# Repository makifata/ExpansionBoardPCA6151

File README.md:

# ExpansionBoardPCA6151
PCA-6151 does work with 5V / 12V supply with four pin connector. However, 
Peripheral board on ISA bus will need negative voltage such as -12 or -5V. 
This Repo is the custom ISA expansion board which distribute -12V and -5V from ATX power.

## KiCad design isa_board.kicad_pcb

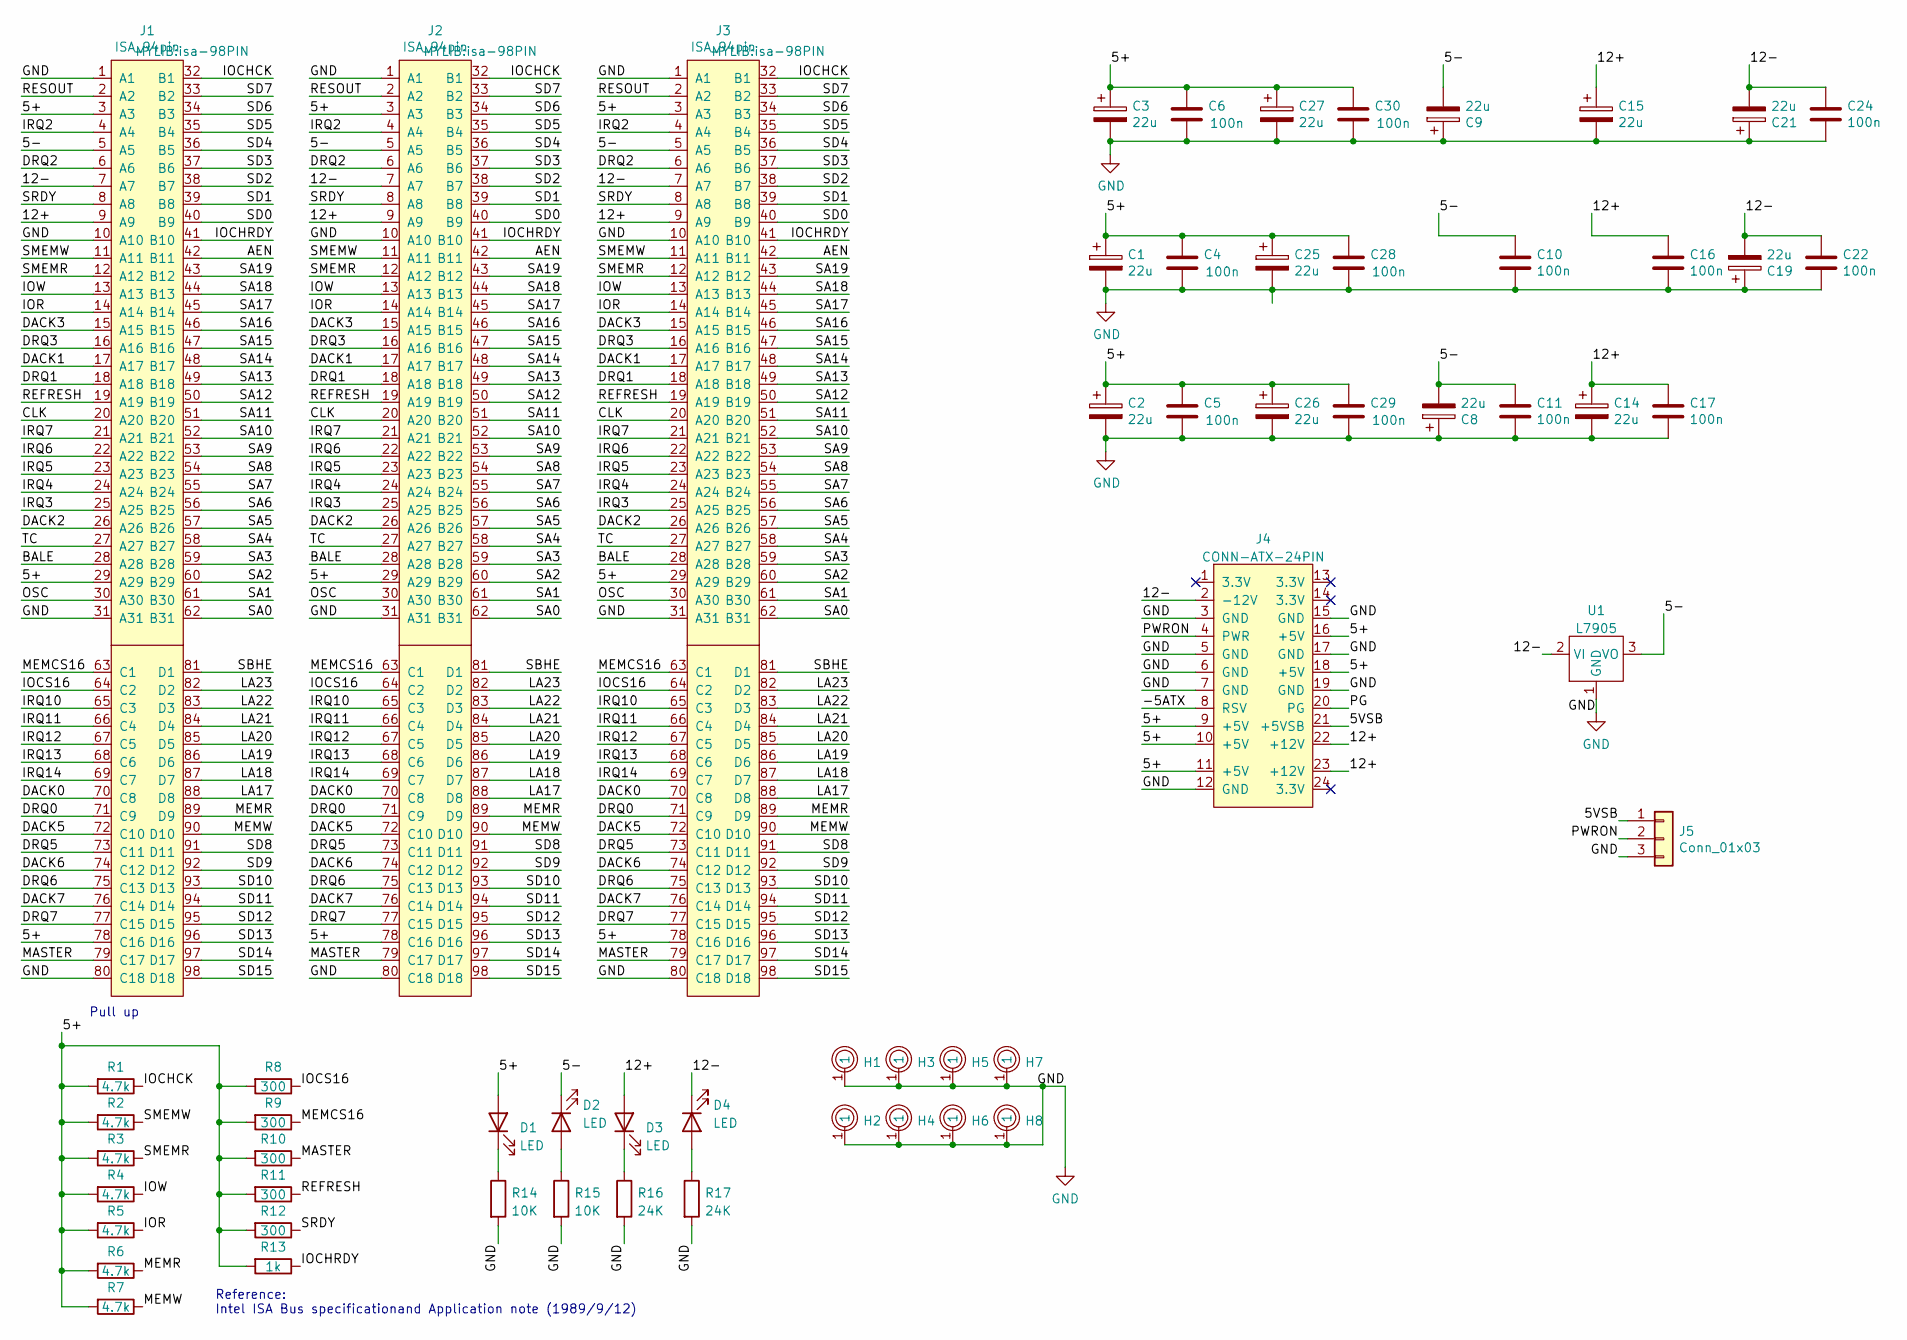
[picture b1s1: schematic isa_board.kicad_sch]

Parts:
C1, C2, C3, C8, C9, C14, C15, C19, C21, C25, C26, C27: 22u; CP_Radial_D5.0mm_P2.00mm
C4, C5, C6, C10, C11, C16, C17, C22, C24, C28, C29, C30: 100n; C_Disc_D4.7mm_W2.5mm_P5.00mm
D1, D2, D3, D4: LED; D_0805_2012Metric_Pad1.15x1.40mm_HandSolder
H1, H2, H3, H4, H5, H6, H7, H8: MountHole; RightAngle
J1, J2, J3: ISA_94pin; isa-98PIN
J4: CONN-ATX-24PIN; atx-24PIN
J5: Conn_01x03; PinHeader_1x03_P2.54mm_Vertical
R1, R2, R3, R4, R5, R6, R7: 4.7k; R_Axial_DIN0309_L9.0mm_D3.2mm_P12.70mm_Horizontal
R8, R9, R10, R11, R12: 300; R_Axial_DIN0309_L9.0mm_D3.2mm_P12.70mm_Horizontal
R13: 1k; R_Axial_DIN0309_L9.0mm_D3.2mm_P12.70mm_Horizontal
R14, R15: 10K; R_0603_1608Metric_Pad0.98x0.95mm_HandSolder
R16, R17: 24K; R_0603_1608Metric_Pad0.98x0.95mm_HandSolder
U1: L7905; L7905ACD2T-TR

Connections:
/5+: C1.1, C2.1, C3.1, C4.1, C5.1, C6.1, C25.1, C26.1, C27.1, C28.1, C29.1, C30.1, D1.2 (A), J1.3 (A3), J1.29 (A29), J1.78 (C16), J2.3 (A3), J2.29 (A29), J2.78 (C16), J3.3 (A3), J3.29 (A29), J3.78 (C16), J4.9 (+5V), J4.10 (+5V), J4.11 (+5V), J4.16 (+5V), J4.18 (+5V), R1.2, R2.2, R3.2, R4.2, R5.2, R6.2, R7.2, R8.2, R9.2, R10.2, R11.2, R12.2, R13.2
/5VSB: J4.21 (+5VSB), J5.1
/12+: C14.1, C15.1, C16.1, C17.1, D3.2 (A), J1.9 (A9), J2.9 (A9), J3.9 (A9), J4.22 (+12V), J4.23 (+12V)
/-5ATX: J4.8 (RSV)
/AEN: J1.42 (B11), J2.42 (B11), J3.42 (B11)
/BALE: J1.28 (A28), J2.28 (A28), J3.28 (A28)
/CLK: J1.20 (A20), J2.20 (A20), J3.20 (A20)
/DACK0: J1.70 (C8), J2.70 (C8), J3.70 (C8)
/DACK1: J1.17 (A17), J2.17 (A17), J3.17 (A17)
/DACK2: J1.26 (A26), J2.26 (A26), J3.26 (A26)
/DACK3: J1.15 (A15), J2.15 (A15), J3.15 (A15)
/DACK5: J1.72 (C10), J2.72 (C10), J3.72 (C10)
/DACK6: J1.74 (C12), J2.74 (C12), J3.74 (C12)
/DACK7: J1.76 (C14), J2.76 (C14), J3.76 (C14)
/DRQ0: J1.71 (C9), J2.71 (C9), J3.71 (C9)
/DRQ1: J1.18 (A18), J2.18 (A18), J3.18 (A18)
/DRQ2: J1.6 (A6), J2.6 (A6), J3.6 (A6)
/DRQ3: J1.16 (A16), J2.16 (A16), J3.16 (A16)
/DRQ5: J1.73 (C11), J2.73 (C11), J3.73 (C11)
/DRQ6: J1.75 (C13), J2.75 (C13), J3.75 (C13)
/DRQ7: J1.77 (C15), J2.77 (C15), J3.77 (C15)
/IOCHCK: J1.32 (B1), J2.32 (B1), J3.32 (B1), R1.1
/IOCHRDY: J1.41 (B10), J2.41 (B10), J3.41 (B10), R13.1
/IOCS16: J1.64 (C2), J2.64 (C2), J3.64 (C2), R8.1
/IOR: J1.14 (A14), J2.14 (A14), J3.14 (A14), R5.1
/IOW: J1.13 (A13), J2.13 (A13), J3.13 (A13), R4.1
/IRQ2: J1.4 (A4), J2.4 (A4), J3.4 (A4)
/IRQ3: J1.25 (A25), J2.25 (A25), J3.25 (A25)
/IRQ4: J1.24 (A24), J2.24 (A24), J3.24 (A24)
/IRQ5: J1.23 (A23), J2.23 (A23), J3.23 (A23)
/IRQ6: J1.22 (A22), J2.22 (A22), J3.22 (A22)
/IRQ7: J1.21 (A21), J2.21 (A21), J3.21 (A21)
/IRQ10: J1.65 (C3), J2.65 (C3), J3.65 (C3)
/IRQ11: J1.66 (C4), J2.66 (C4), J3.66 (C4)
/IRQ12: J1.67 (C5), J2.67 (C5), J3.67 (C5)
/IRQ13: J1.68 (C6), J2.68 (C6), J3.68 (C6)
/IRQ14: J1.69 (C7), J2.69 (C7), J3.69 (C7)
/LA17: J1.88 (D8), J2.88 (D8), J3.88 (D8)
/LA18: J1.87 (D7), J2.87 (D7), J3.87 (D7)
/LA19: J1.86 (D6), J2.86 (D6), J3.86 (D6)
/LA20: J1.85 (D5), J2.85 (D5), J3.85 (D5)
/LA21: J1.84 (D4), J2.84 (D4), J3.84 (D4)
/LA22: J1.83 (D3), J2.83 (D3), J3.83 (D3)
/LA23: J1.82 (D2), J2.82 (D2), J3.82 (D2)
/MASTER: J1.79 (C17), J2.79 (C17), J3.79 (C17), R10.1
/MEMCS16: J1.63 (C1), J2.63 (C1), J3.63 (C1), R9.1
/MEMR: J1.89 (D9), J2.89 (D9), J3.89 (D9), R6.1
/MEMW: J1.90 (D10), J2.90 (D10), J3.90 (D10), R7.1
/OSC: J1.30 (A30), J2.30 (A30), J3.30 (A30)
/PG: J4.20 (PG)
/PWRON: J4.4 (PWR), J5.2
/REFRESH: J1.19 (A19), J2.19 (A19), J3.19 (A19), R11.1
/RESOUT: J1.2 (A2), J2.2 (A2), J3.2 (A2)
/SA0: J1.62 (B31), J2.62 (B31), J3.62 (B31)
/SA1: J1.61 (B30), J2.61 (B30), J3.61 (B30)
/SA2: J1.60 (B29), J2.60 (B29), J3.60 (B29)
/SA3: J1.59 (B28), J2.59 (B28), J3.59 (B28)
/SA4: J1.58 (B27), J2.58 (B27), J3.58 (B27)
/SA5: J1.57 (B26), J2.57 (B26), J3.57 (B26)
/SA6: J1.56 (B25), J2.56 (B25), J3.56 (B25)
/SA7: J1.55 (B24), J2.55 (B24), J3.55 (B24)
/SA8: J1.54 (B23), J2.54 (B23), J3.54 (B23)
/SA9: J1.53 (B22), J2.53 (B22), J3.53 (B22)
/SA10: J1.52 (B21), J2.52 (B21), J3.52 (B21)
/SA11: J1.51 (B20), J2.51 (B20), J3.51 (B20)
/SA12: J1.50 (B19), J2.50 (B19), J3.50 (B19)
/SA13: J1.49 (B18), J2.49 (B18), J3.49 (B18)
/SA14: J1.48 (B17), J2.48 (B17), J3.48 (B17)
/SA15: J1.47 (B16), J2.47 (B16), J3.47 (B16)
/SA16: J1.46 (B15), J2.46 (B15), J3.46 (B15)
/SA17: J1.45 (B14), J2.45 (B14), J3.45 (B14)
/SA18: J1.44 (B13), J2.44 (B13), J3.44 (B13)
/SA19: J1.43 (B12), J2.43 (B12), J3.43 (B12)
/SBHE: J1.81 (D1), J2.81 (D1), J3.81 (D1)
/SD0: J1.40 (B9), J2.40 (B9), J3.40 (B9)
/SD1: J1.39 (B8), J2.39 (B8), J3.39 (B8)
/SD2: J1.38 (B7), J2.38 (B7), J3.38 (B7)
/SD3: J1.37 (B6), J2.37 (B6), J3.37 (B6)
/SD4: J1.36 (B5), J2.36 (B5), J3.36 (B5)
/SD5: J1.35 (B4), J2.35 (B4), J3.35 (B4)
/SD6: J1.34 (B3), J2.34 (B3), J3.34 (B3)
/SD7: J1.33 (B2), J2.33 (B2), J3.33 (B2)
/SD8: J1.91 (D11), J2.91 (D11), J3.91 (D11)
/SD9: J1.92 (D12), J2.92 (D12), J3.92 (D12)
/SD10: J1.93 (D13), J2.93 (D13), J3.93 (D13)
/SD11: J1.94 (D14), J2.94 (D14), J3.94 (D14)
/SD12: J1.95 (D15), J2.95 (D15), J3.95 (D15)
/SD13: J1.96 (D16), J2.96 (D16), J3.96 (D16)
/SD14: J1.97 (D17), J2.97 (D17), J3.97 (D17)
/SD15: J1.98 (D18), J2.98 (D18), J3.98 (D18)
/SMEMR: J1.12 (A12), J2.12 (A12), J3.12 (A12), R3.1
/SMEMW: J1.11 (A11), J2.11 (A11), J3.11 (A11), R2.1
/SRDY: J1.8 (A8), J2.8 (A8), J3.8 (A8), R12.1
/TC: J1.27 (A27), J2.27 (A27), J3.27 (A27)
GND: C1.2, C2.2, C3.2, C4.2, C5.2, C6.2, C8.1, C9.1, C10.2, C11.2, C14.2, C15.2, C16.2, C17.2, C19.1, C21.1, C22.2, C24.2, C25.2, C26.2, C27.2, C28.2, C29.2, C30.2, H1.1, H2.1, H3.1, H4.1, H5.1, H6.1, H7.1, H8.1, J1.1 (A1), J1.10 (A10), J1.31 (A31), J1.80 (C18), J2.1 (A1), J2.10 (A10), J2.31 (A31), J2.80 (C18), J3.1 (A1), J3.10 (A10), J3.31 (A31), J3.80 (C18), J4.3 (GND), J4.5 (GND), J4.6 (GND), J4.7 (GND), J4.12 (GND), J4.15 (GND), J4.17 (GND), J4.19 (GND), J5.3, R14.2, R15.2, R16.2, R17.2, U1.1 (GND)
unnamed: D1.1 (K), R14.1
unnamed: D3.1 (K), R16.1

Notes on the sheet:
Reference: Intel ISA Bus specificationand Application note (1989/9/12)
Pull up

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
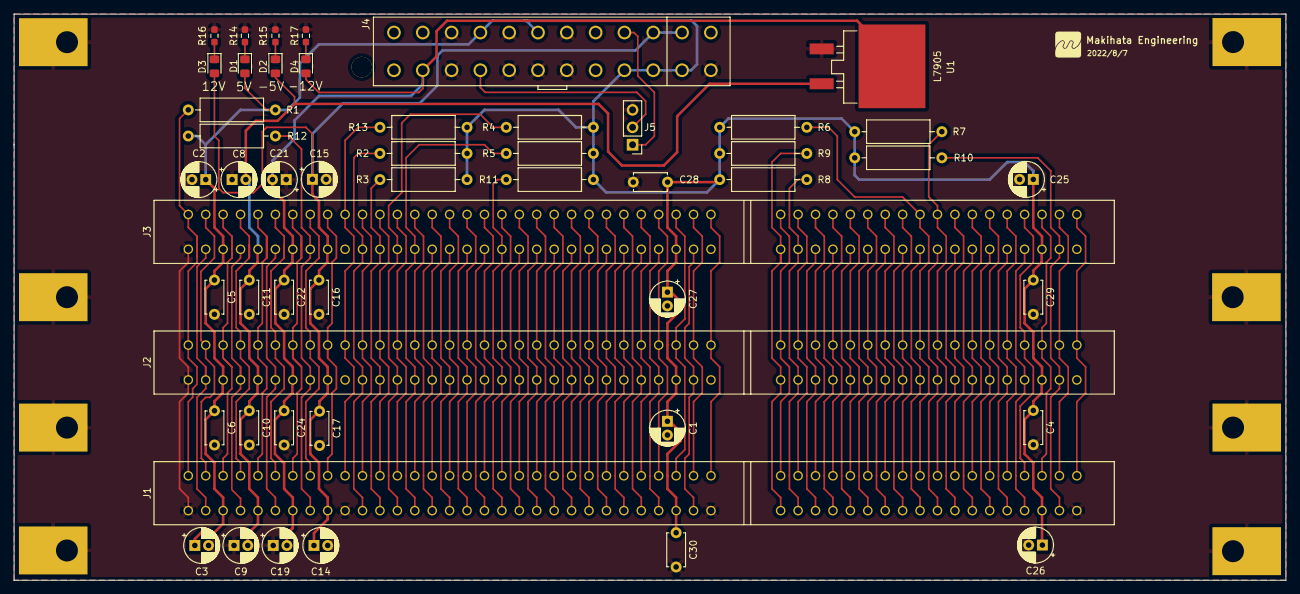
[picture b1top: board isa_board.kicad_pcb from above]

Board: 2 copper layers, 185.4 x 82.5 mm, 59 parts (0 on the bottom side), 99 nets.

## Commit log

2023-05-31 :memo: doc

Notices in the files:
parts and their libraries:
Copyright 2021 Accelerated Designs. All rights reserved.
